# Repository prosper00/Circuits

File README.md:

Some KiCAD drawings I've make, of various useful circuits I've found online or reverse engineered (or adapted from someone else's design)

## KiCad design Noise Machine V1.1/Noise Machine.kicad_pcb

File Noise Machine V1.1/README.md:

# My attempt at an audio noise generator / sleep machine.
It's not 'white' or 'pink' or any particular color of noise - the filter stage shapes the output to whatever you feel sounds best. It's designed as a sleep aid to mask other noises.

### Goals:
- Run on 5V.
- Can provide 10 hours runtime on a small rechargeable USB power pack at moderate volume (so, let's say, we need this circuit to operate at < 100mA)
- Adjustable tone controls
- 'adequate' power output. A few mW to the speaker is quite sufficient to mask ambient sounds.
- uses 'jellybean' components that I have on hand

### Design:
- I settled on an avalanche noise source, running a small current above the breakdown voltage of an NPN be junction. Experimentally, I found that 8-9V is needed for a few of the common transistors I had on hand. I didn't see any significant difference between the few transistors that I tested, but that 12-15V produced much more amplitude.
- This is an audio device, so I don't need or want RF noise. Negative feedback on Q2 is applied with a 1nF capacitor (C3), to kill the RF as close to the source as possible.
- I'm running Q2 off of the 15V rail (more like +12V after diode drops etc.). However, Q2 output is only a few mV anyway and so it doesn't exceed the LM386 input. 
- I added a small adjustable filter section so that I could tune the output to a 'pleasing' sound. It's not super linear, and it does interact with the amplitude somewhat. 
- Because of the 5V supply voltage goal, I needed a low-current source of ~15V. Q3 and Q4 generate a square wave and power a small charge pump. A lot of the components in this voltage booster are less than optimal, though I did tweak them somewhat with the goal of producing sufficient current output, at reasonable efficiency. However, it works with the values I've chosen, more or less, though I did have some problems with the multivibrator failing to multivibrate. I added some startup diodes to increase its reliability, however, there's got to be a more elegant solution. 
- I used an LM386 to handle the output amplification, because I have a bunch. It provides more than sufficient output power. Really, it's overkill. 
- not shown in the circuit diagram is a 100uF and a 100nF decoupling capacitor near to where power comes into the PCB, right by the LM386 pins. This greatly helped with the multivibrator startup problems I had, and cleaned up its output signal. Using 31AWG magnet wire for the 'traces' on the protoboard is probably not the best idea, at least for the +5V/power GND connections.

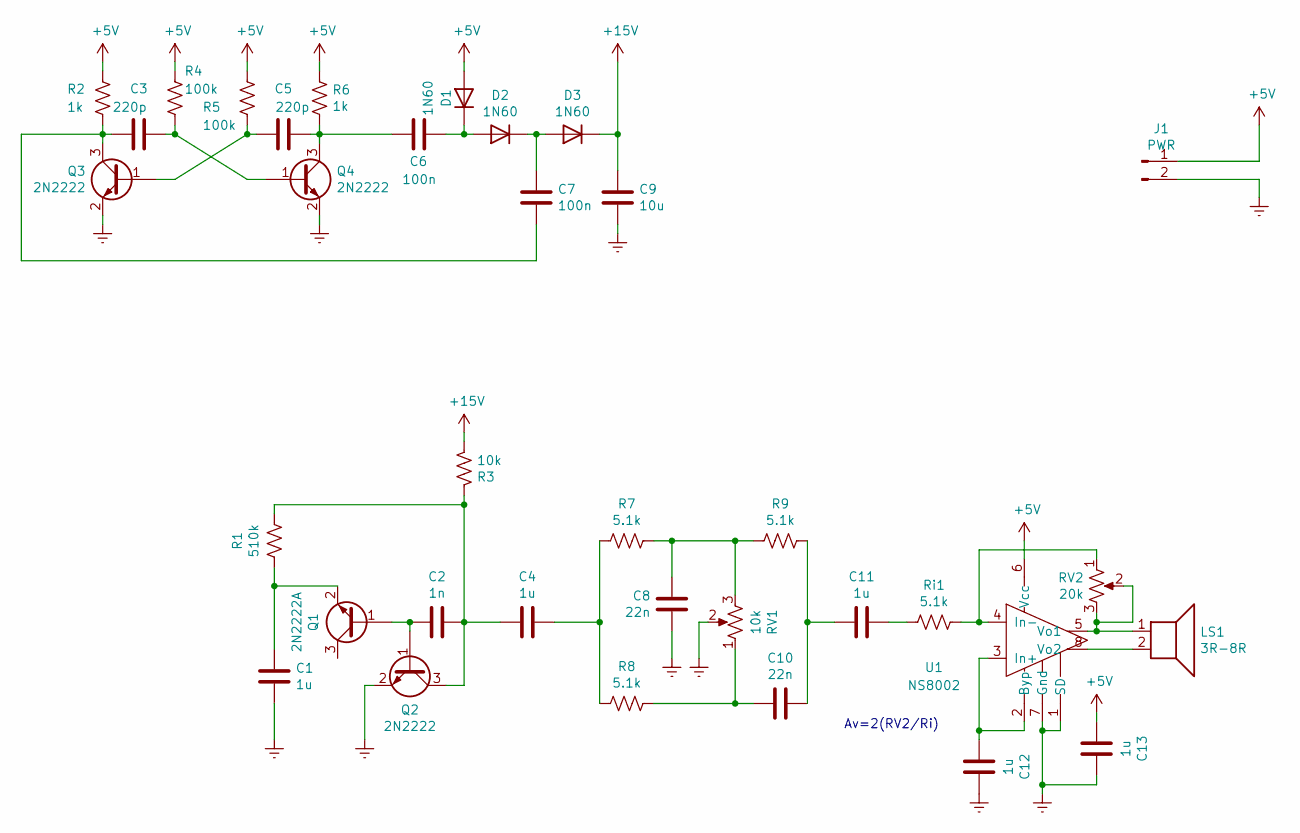
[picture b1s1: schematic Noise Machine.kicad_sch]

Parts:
C1, C4, C11, C12, C13: 1u; C_0603_1608Metric_Pad1.08x0.95mm_HandSolder
C2: 1n; C_0603_1608Metric_Pad1.08x0.95mm_HandSolder
C3, C5: 220p; C_0603_1608Metric_Pad1.08x0.95mm_HandSolder
C6, C7: 100n; C_0603_1608Metric_Pad1.08x0.95mm_HandSolder
C8, C10: 22n; C_0603_1608Metric_Pad1.08x0.95mm_HandSolder
C9: 10u; C_0603_1608Metric_Pad1.08x0.95mm_HandSolder
D1, D2, D3: 1N60; D_DO-35_SOD27_P5.08mm_Vertical_AnodeUp
J1: PWR; PinHeader_1x02_P2.54mm_Vertical
LS1: 3R-8R; PinHeader_1x02_P2.54mm_Vertical
Q1: 2N2222A; SOT-23
Q2, Q3, Q4: 2N2222; SOT-23
R1: 510k; R_0603_1608Metric_Pad0.98x0.95mm_HandSolder
R2, R6: 1k; R_0603_1608Metric_Pad0.98x0.95mm_HandSolder
R3: 10k; R_0603_1608Metric_Pad0.98x0.95mm_HandSolder
R4, R5: 100k; R_0603_1608Metric_Pad0.98x0.95mm_HandSolder
R7, R8, R9: 5.1k; R_0603_1608Metric_Pad0.98x0.95mm_HandSolder
RV1: 10k; PinHeader_1x03_P2.54mm_Vertical
RV2: 20k; PinHeader_1x02_P2.54mm_Vertical
Ri1: 5.1k; R_0603_1608Metric_Pad0.98x0.95mm_HandSolder
U1: NS8002; SO-8_3.9x4.9mm_P1.27mm

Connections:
+5V: C13.2, D1.2 (A), J1.1, R2.1, R4.1, R5.1, R6.1, U1.6 (Vcc)
+15V: C9.1, D3.1 (K), R3.2
Earth: C1.2, C8.1, C9.2, C12.1, C13.1, J1.2, Q2.2 (E), Q3.2 (E), Q4.2 (E), RV1.2, U1.1 (SD), U1.7 (Gnd)
unnamed: C1.1, Q1.2 (E), R1.2
unnamed: C2.1, C4.2, Q2.3 (C), R1.1, R3.1
unnamed: C2.2, Q1.1 (B), Q2.1 (B)
unnamed: C3.1, C7.2, Q3.3 (C), R2.2
unnamed: C3.2, Q4.1 (B), R4.2
unnamed: C4.1, R7.2, R8.2
unnamed: C5.1, C6.1, Q4.3 (C), R6.2
unnamed: C5.2, Q3.1 (B), R5.2
unnamed: C6.2, D1.1 (K), D2.2 (A)
unnamed: C7.1, D2.1 (K), D3.2 (A)
unnamed: C8.2, R7.1, R9.2, RV1.3
unnamed: C10.1, R8.1, RV1.1
unnamed: C10.2, C11.1, R9.1
unnamed: C11.2, Ri1.2
unnamed: C12.2, U1.2 (Byp), U1.3 (In+)
unnamed: LS1.1, RV2.2, RV2.3, U1.5 (Vo1)
unnamed: LS1.2, U1.8 (Vo2)
unnamed: RV2.1, Ri1.1, U1.4 (In-)

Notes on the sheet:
Av=2(RV2/Ri)

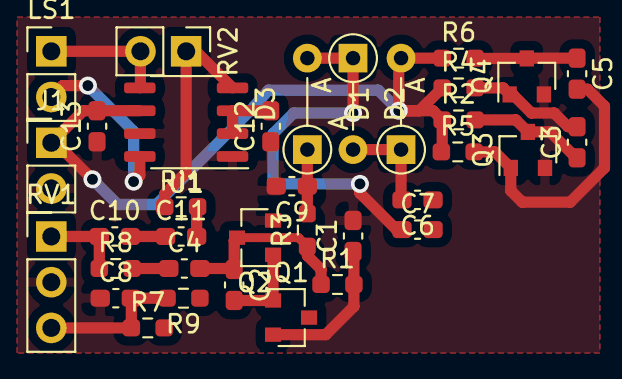
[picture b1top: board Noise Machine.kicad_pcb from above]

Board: 2 copper layers, 35 parts (0 on the bottom side), 21 nets.

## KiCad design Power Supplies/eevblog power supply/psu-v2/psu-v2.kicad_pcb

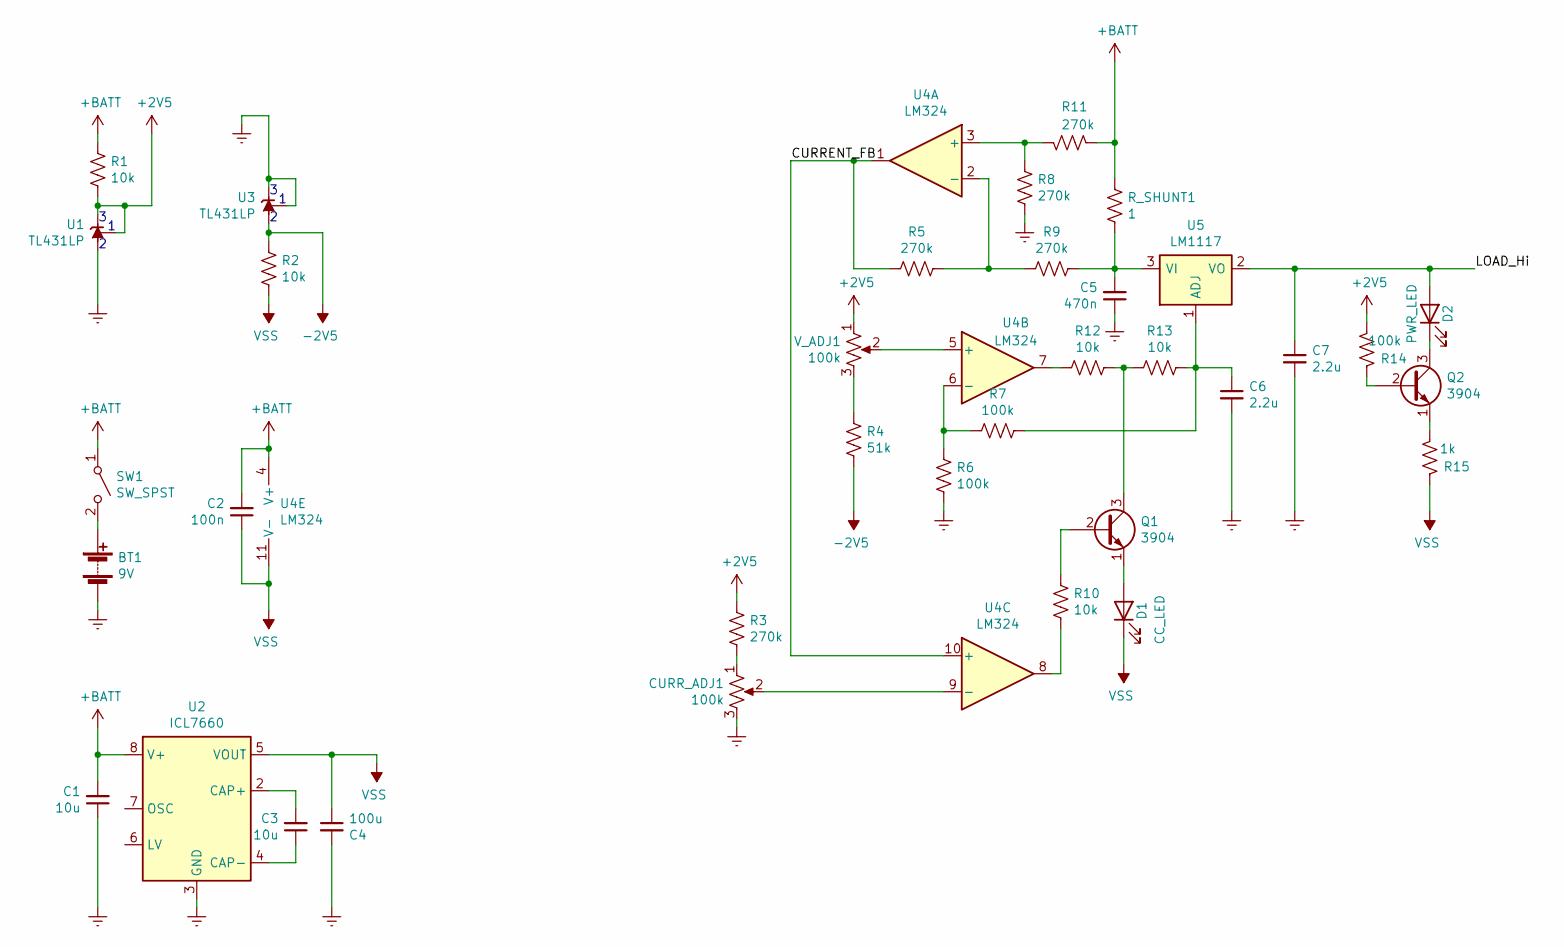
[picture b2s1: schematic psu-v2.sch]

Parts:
BT1: 9V; TerminalBlock_Altech_AK300-2_P5.00mm
C1, C3: 10u; C_Disc_D5.1mm_W3.2mm_P5.00mm
C2: 100n; C_Disc_D5.1mm_W3.2mm_P5.00mm
C4: 100u; C_Radial_D6.3mm_H7.0mm_P2.50mm
C5: 470n; C_Disc_D5.1mm_W3.2mm_P5.00mm
C6, C7: 2.2u; C_Disc_D5.1mm_W3.2mm_P5.00mm
CURR_ADJ1: 100k; Potentiometer_Alps_RK09K_Single_Horizontal
D1: CC_LED; LED_D3.0mm
D2: PWR_LED; LED_D3.0mm
Q1, Q2: 3904; TO-92L_Inline
R1, R2, R10, R12, R13: 10k; R_Axial_DIN0204_L3.6mm_D1.6mm_P5.08mm_Horizontal
R3, R5, R8, R9, R11: 270k; R_Axial_DIN0204_L3.6mm_D1.6mm_P5.08mm_Horizontal
R4: 51k; R_Axial_DIN0204_L3.6mm_D1.6mm_P5.08mm_Horizontal
R6, R7, R14: 100k; R_Axial_DIN0204_L3.6mm_D1.6mm_P5.08mm_Horizontal
R15: 1k; R_Axial_DIN0204_L3.6mm_D1.6mm_P5.08mm_Horizontal
R_SHUNT1: 1; R_Axial_DIN0414_L11.9mm_D4.5mm_P15.24mm_Horizontal
SW1: SW_SPST; PinHeader_1x02_P2.54mm_Vertical
U1, U3: TL431LP; TO-92_Inline
U2: ICL7660; DIP-8_W7.62mm_Socket
U4: LM324; DIP-14_W7.62mm_Socket
U5: LM1117; SOT-223-3_TabPin2
V_ADJ1: 100k; Potentiometer_Alps_RK09K_Single_Horizontal

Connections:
+2V5: R1.1, R3.2, R14.2, U1.1 (REF), U1.3 (K), V_ADJ1.1
+BATT: C1.2, C2.2, R1.2, R11.2, R_SHUNT1.2, SW1.1 (A), U2.8 (V+), U4.4 (V+)
-2V5: R2.2, R4.1, U3.2 (A)
/CURRENT_FB: R5.2, U4.1, U4.10 (+)
/LOAD_Hi: C7.1, D2.2 (A), U5.2 (VO)
Earth: BT1.2 (-), C1.1, C4.2, C5.1, C6.2, C7.2, CURR_ADJ1.3, R6.1, R8.1, U1.2 (A), U2.3 (GND), U3.1 (REF), U3.3 (K)
unnamed: BT1.1 (+), SW1.2 (B)
unnamed: C3.1, U2.4 (CAP-)
unnamed: C3.2, U2.2 (CAP+)
unnamed: C5.2, R9.1, R_SHUNT1.1, U5.3 (VI)
unnamed: C6.1, R7.2, R13.2, U5.1 (ADJ)
unnamed: CURR_ADJ1.1, R3.1
unnamed: CURR_ADJ1.2, U4.9 (-)
unnamed: D1.2 (A), Q1.1 (E)
unnamed: D2.1 (K), Q2.3 (C)
unnamed: Q1.2 (B), R10.1
unnamed: Q1.3 (C), R12.2, R13.1
unnamed: Q2.1 (E), R15.2
unnamed: Q2.2 (B), R14.1
unnamed: R4.2, V_ADJ1.3
unnamed: R5.1, R9.2, U4.2 (-)
unnamed: R6.2, R7.1, U4.6 (-)
unnamed: R10.2, U4.8
unnamed: R8.2, R11.1, U4.3 (+)
unnamed: R12.1, U4.7
unnamed: U4.5 (+), V_ADJ1.2
VSS: C2.1, C4.1, D1.1 (K), R2.1, R15.1, U2.5 (VOUT), U4.11 (V-)

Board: 2 copper layers, 36 parts (0 on the bottom side), 27 nets, no tracks yet.

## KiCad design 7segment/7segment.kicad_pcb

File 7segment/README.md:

see the project page on pcbway ( https://www.pcbway.com/project/shareproject/discrete_7_segment_LED.html ) if you want to order one. Or, use the provided gerber files with the manufacturer of your choosing

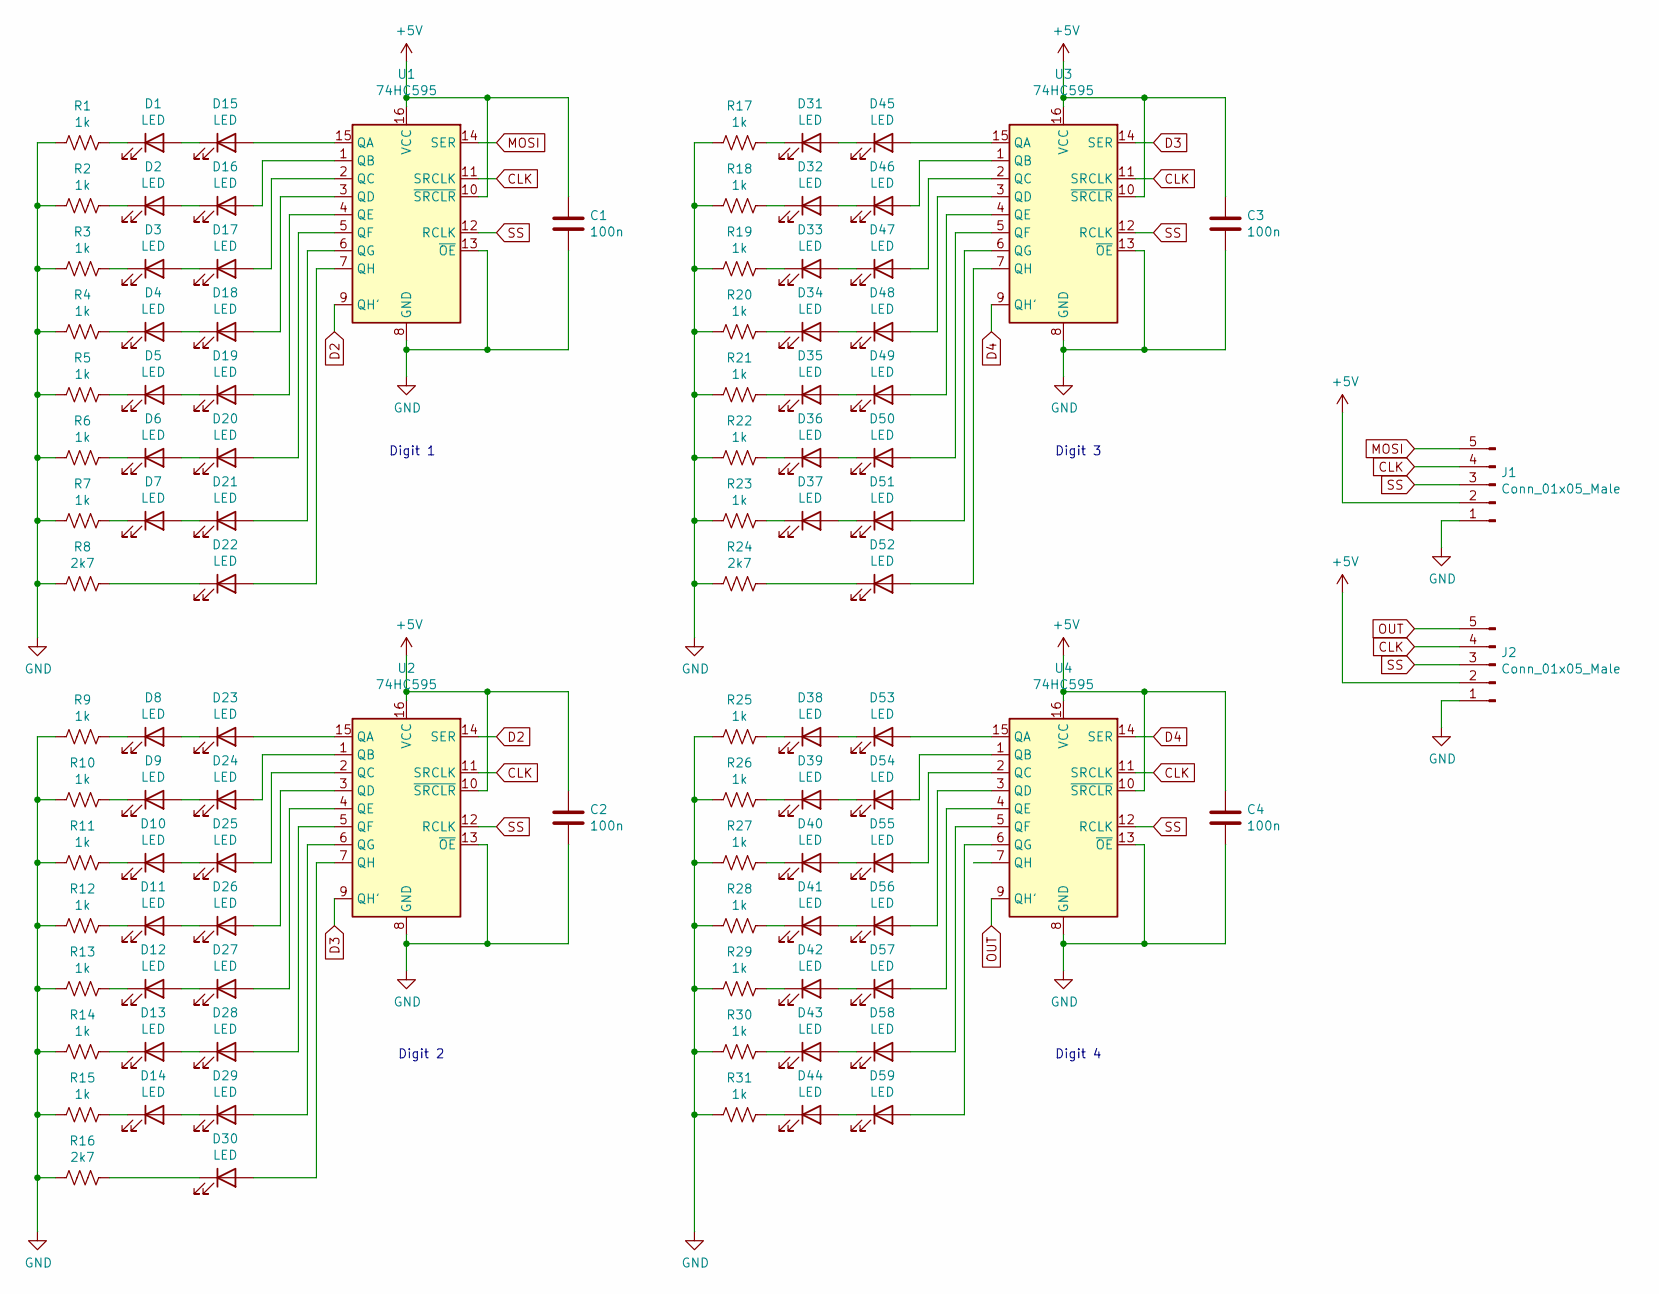
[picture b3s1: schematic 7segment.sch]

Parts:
C1, C2, C3, C4: 100n; C_Disc_D4.7mm_W2.5mm_P5.00mm
D1, D2, D3, D4, D5, D6, D7, D8, D9, D10, D11, D12, D13, D14, D15, D16, D17, D18, D19, D20, D21, D22, D23, D24, D25, D26, D27, D28, D29, D30, D31, D32, D33, D34, D35, D36, D37, D38, D39, D40, D41, D42, D43, D44, D45, D46, D47, D48, D49, D50, D51, D52, D53, D54, D55, D56, D57, D58, D59: LED; LED_D3.0mm
J1, J2: Conn_01x05_Male; PinHeader_1x05_P2.54mm_Vertical
R1, R2, R3, R4, R5, R6, R7, R9, R10, R11, R12, R13, R14, R15, R17, R18, R19, R20, R21, R22, R23, R25, R26, R27, R28, R29, R30, R31: 1k; R_Axial_DIN0204_L3.6mm_D1.6mm_P5.08mm_Horizontal
R8, R16, R24: 2k7; R_Axial_DIN0204_L3.6mm_D1.6mm_P5.08mm_Horizontal
U1, U2, U3, U4: 74HC595; DIP-16_W7.62mm

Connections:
+5V: C1.1, C2.1, C3.1, C4.1, J1.2, J2.2, U1.10 (~SRCLR), U1.16 (VCC), U2.10 (~SRCLR), U2.16 (VCC), U3.10 (~SRCLR), U3.16 (VCC), U4.10 (~SRCLR), U4.16 (VCC)
CLK: J1.4, J2.4, U1.11 (SRCLK), U2.11 (SRCLK), U3.11 (SRCLK), U4.11 (SRCLK)
D2: U1.9 (QH'), U2.14 (SER)
D3: U2.9 (QH'), U3.14 (SER)
D4: U3.9 (QH'), U4.14 (SER)
GND: C1.2, C2.2, C3.2, C4.2, J1.1, J2.1, R1.2, R2.2, R3.2, R4.2, R5.2, R6.2, R7.2, R8.2, R9.2, R10.2, R11.2, R12.2, R13.2, R14.2, R15.2, R16.2, R17.2, R18.2, R19.2, R20.2, R21.2, R22.2, R23.2, R24.2, R25.2, R26.2, R27.2, R28.2, R29.2, R30.2, R31.2, U1.8 (GND), U1.13 (~OE), U2.8 (GND), U2.13 (~OE), U3.8 (GND), U3.13 (~OE), U4.8 (GND), U4.13 (~OE)
MOSI: J1.5, U1.14 (SER)
unnamed: D1.1 (K), R1.1
unnamed: D1.2 (A), D15.1 (K)
unnamed: D2.1 (K), R2.1
unnamed: D3.1 (K), R3.1
unnamed: D4.1 (K), R4.1
unnamed: D5.1 (K), R5.1
unnamed: D6.1 (K), R6.1
unnamed: D7.1 (K), R7.1
unnamed: D8.1 (K), R9.1
unnamed: D9.1 (K), R10.1
unnamed: D10.1 (K), R11.1
unnamed: D10.2 (A), D25.1 (K)
unnamed: D11.1 (K), R12.1
unnamed: D11.2 (A), D26.1 (K)
unnamed: D12.1 (K), R13.1
unnamed: D12.2 (A), D27.1 (K)
unnamed: D13.1 (K), R14.1
unnamed: D13.2 (A), D28.1 (K)
unnamed: D14.1 (K), R15.1
unnamed: D14.2 (A), D29.1 (K)
unnamed: D15.2 (A), U1.15 (QA)
unnamed: D2.2 (A), D16.1 (K)
unnamed: D16.2 (A), U1.1 (QB)
unnamed: D3.2 (A), D17.1 (K)
unnamed: D17.2 (A), U1.2 (QC)
unnamed: D4.2 (A), D18.1 (K)
unnamed: D18.2 (A), U1.3 (QD)
unnamed: D5.2 (A), D19.1 (K)
unnamed: D19.2 (A), U1.4 (QE)
unnamed: D6.2 (A), D20.1 (K)
unnamed: D20.2 (A), U1.5 (QF)
unnamed: D7.2 (A), D21.1 (K)
unnamed: D21.2 (A), U1.6 (QG)
unnamed: D22.1 (K), R8.1
unnamed: D22.2 (A), U1.7 (QH)
unnamed: D8.2 (A), D23.1 (K)
unnamed: D23.2 (A), U2.15 (QA)
unnamed: D9.2 (A), D24.1 (K)
unnamed: D24.2 (A), U2.1 (QB)
unnamed: D25.2 (A), U2.2 (QC)
unnamed: D26.2 (A), U2.3 (QD)
unnamed: D27.2 (A), U2.4 (QE)
unnamed: D28.2 (A), U2.5 (QF)
unnamed: D29.2 (A), U2.6 (QG)
unnamed: D30.1 (K), R16.1
unnamed: D30.2 (A), U2.7 (QH)
unnamed: D31.1 (K), R17.1
unnamed: D31.2 (A), D45.1 (K)
unnamed: D32.1 (K), R18.1
unnamed: D32.2 (A), D46.1 (K)
unnamed: D33.1 (K), R19.1
unnamed: D33.2 (A), D47.1 (K)
unnamed: D34.1 (K), R20.1
unnamed: D34.2 (A), D48.1 (K)
unnamed: D35.1 (K), R21.1
unnamed: D35.2 (A), D49.1 (K)
unnamed: D36.1 (K), R22.1
unnamed: D36.2 (A), D50.1 (K)
unnamed: D37.1 (K), R23.1
unnamed: D37.2 (A), D51.1 (K)
unnamed: D38.1 (K), R25.1
unnamed: D38.2 (A), D53.1 (K)
unnamed: D39.1 (K), R26.1
unnamed: D39.2 (A), D54.1 (K)
unnamed: D40.1 (K), R27.1
unnamed: D40.2 (A), D55.1 (K)
unnamed: D41.1 (K), R28.1
unnamed: D41.2 (A), D56.1 (K)
unnamed: D42.1 (K), R29.1
unnamed: D42.2 (A), D57.1 (K)
unnamed: D43.1 (K), R30.1
unnamed: D43.2 (A), D58.1 (K)
unnamed: D44.1 (K), R31.1
unnamed: D44.2 (A), D59.1 (K)
unnamed: D45.2 (A), U3.15 (QA)
unnamed: D46.2 (A), U3.1 (QB)
unnamed: D47.2 (A), U3.2 (QC)
unnamed: D48.2 (A), U3.3 (QD)
unnamed: D49.2 (A), U3.4 (QE)
unnamed: D50.2 (A), U3.5 (QF)
unnamed: D51.2 (A), U3.6 (QG)
unnamed: D52.1 (K), R24.1
unnamed: D52.2 (A), U3.7 (QH)
unnamed: D53.2 (A), U4.15 (QA)
unnamed: D54.2 (A), U4.1 (QB)
unnamed: D55.2 (A), U4.2 (QC)
unnamed: D56.2 (A), U4.3 (QD)
unnamed: D57.2 (A), U4.4 (QE)
unnamed: D58.2 (A), U4.5 (QF)
unnamed: D59.2 (A), U4.6 (QG)
OUT: J2.5, U4.9 (QH')
SS: J1.3, J2.3, U1.12 (RCLK), U2.12 (RCLK), U3.12 (RCLK), U4.12 (RCLK)

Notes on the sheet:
Digit 1
Digit 2
Digit 3
Digit 4

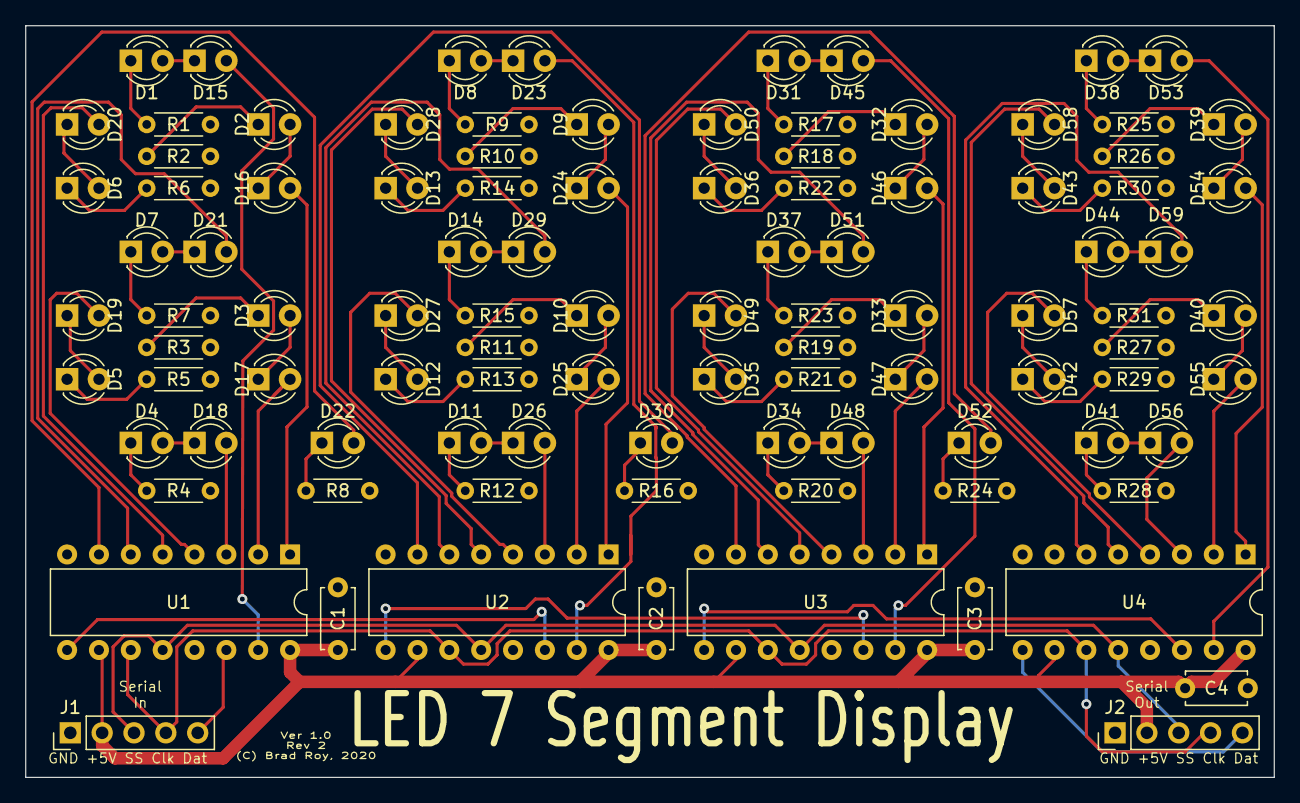
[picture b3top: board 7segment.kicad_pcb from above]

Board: 2 copper layers, 99.6 x 59.9 mm, 100 parts (0 on the bottom side), 99 nets.

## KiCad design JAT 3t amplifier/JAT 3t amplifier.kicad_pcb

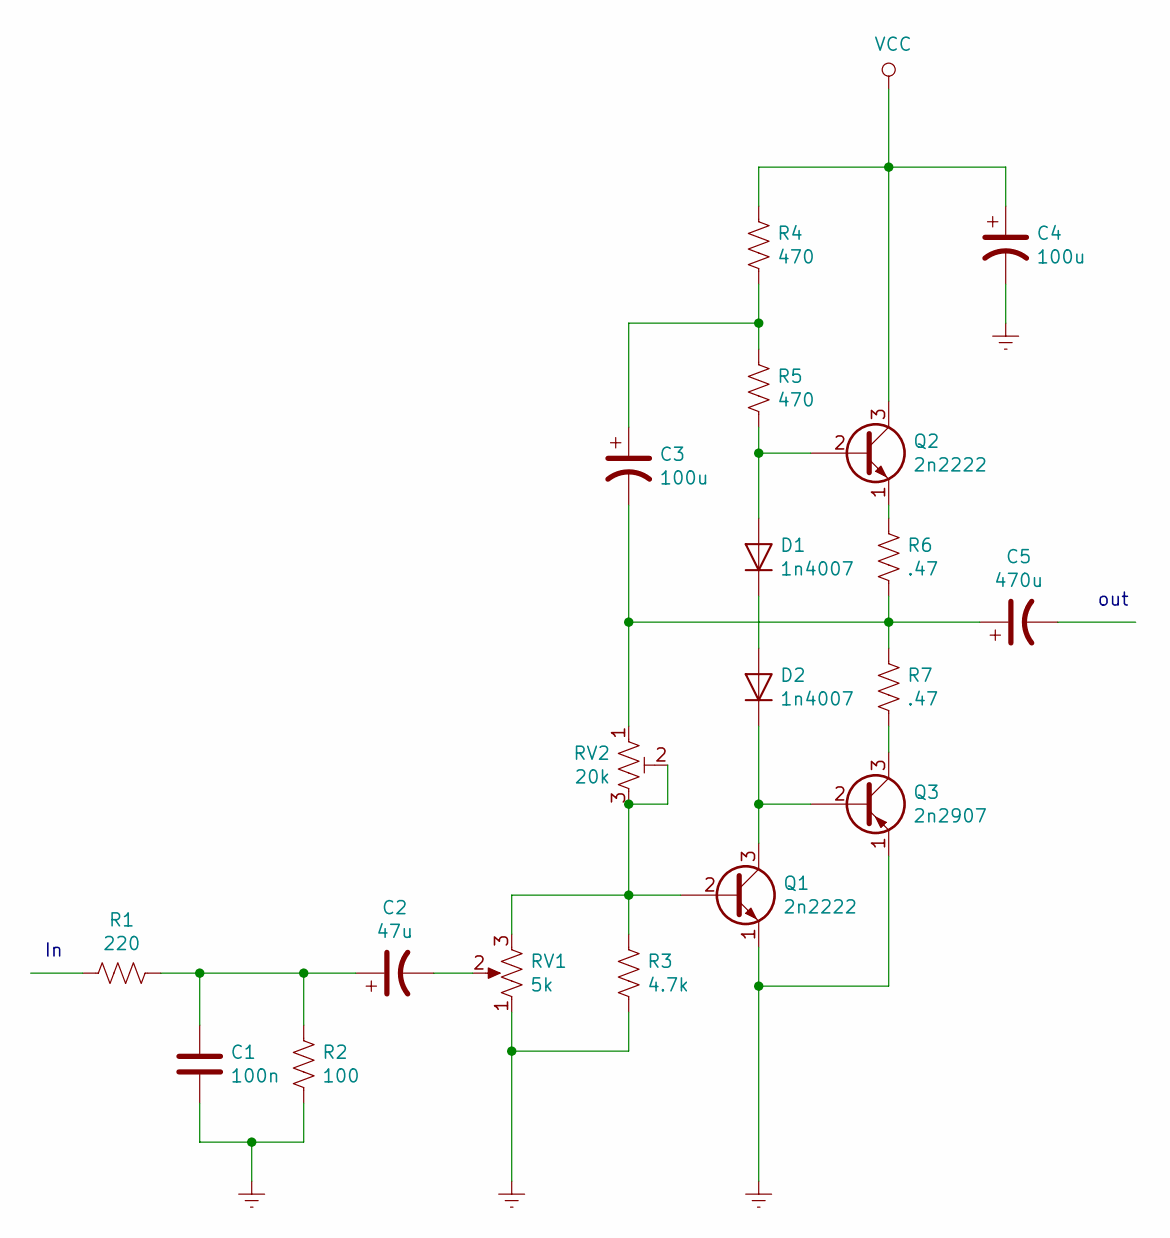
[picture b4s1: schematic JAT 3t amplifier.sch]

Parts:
C1: 100n; CP_Radial_Tantal_D6.0mm_P5.00mm
C2: 47u; CP_Radial_D6.3mm_P2.50mm
C3, C4: 100u; CP_Radial_D6.3mm_P2.50mm
C5: 470u; CP_Radial_D8.0mm_P2.50mm
D1, D2: 1n4007; D_DO-41_SOD81_P7.62mm_Horizontal
Q1, Q2: 2n2222; TO-92
Q3: 2n2907; TO-92
R1: 220; R_Axial_DIN0207_L6.3mm_D2.5mm_P7.62mm_Horizontal
R2: 100; R_Axial_DIN0207_L6.3mm_D2.5mm_P7.62mm_Horizontal
R3: 4.7k; R_Axial_DIN0207_L6.3mm_D2.5mm_P7.62mm_Horizontal
R4, R5: 470; R_Axial_DIN0207_L6.3mm_D2.5mm_P7.62mm_Horizontal
R6, R7: .47; R_Axial_DIN0207_L6.3mm_D2.5mm_P7.62mm_Horizontal
RV1: 5k; Potentiometer_ACP_CA9-H5_Horizontal
RV2: 20k; Potentiometer_ACP_CA9-H5_Horizontal

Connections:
Earth: C1.2, C4.2, Q1.1 (E), Q3.1 (E), R2.1, R3.2, RV1.1
unnamed: C1.1, C2.1, R1.1, R2.2
unnamed: C2.2, RV1.2
unnamed: C3.1, R4.2, R5.1
unnamed: C3.2, C5.1, R6.2, R7.1, RV2.1
unnamed: D1.1 (K), D2.2 (A)
unnamed: D1.2 (A), Q2.2 (B), R5.2
unnamed: D2.1 (K), Q1.3 (C), Q3.2 (B)
unnamed: Q1.2 (B), R3.1, RV1.3, RV2.2, RV2.3
unnamed: Q2.1 (E), R6.1
unnamed: Q3.3 (C), R7.2
VCC: C4.1, Q2.3 (C), R4.1

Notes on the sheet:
out

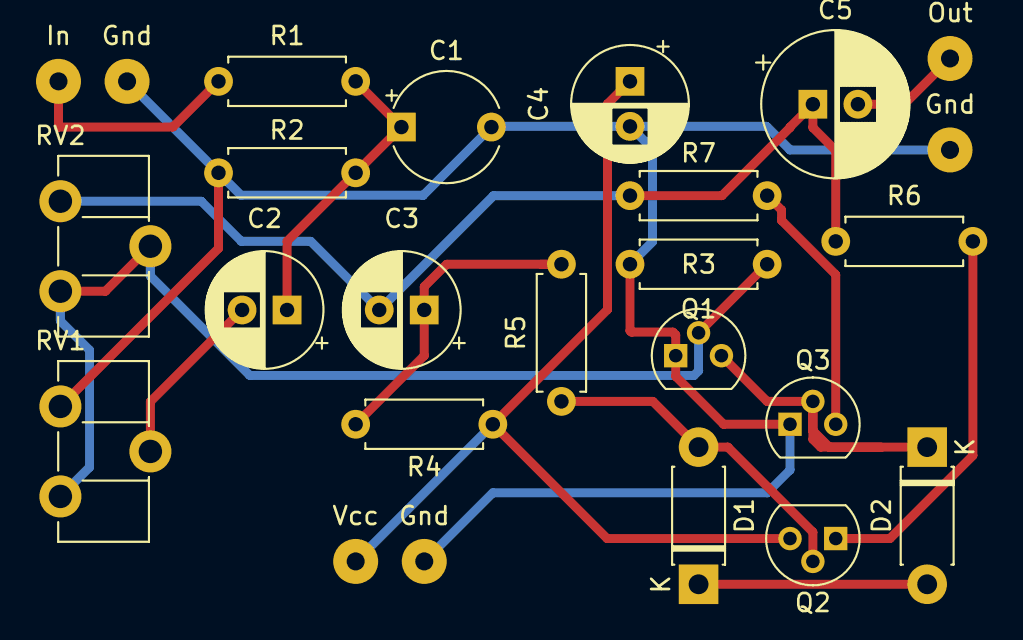
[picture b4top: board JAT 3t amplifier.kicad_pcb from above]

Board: 2 copper layers, 25 parts (0 on the bottom side), 12 nets.

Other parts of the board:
Gnd: SolderWirePad_1x01_Drill1mm
Gnd#2, Gnd#3: SolderWirePad_1x01_Drill1mm
In: SolderWirePad_1x01_Drill1mm
Out: SolderWirePad_1x01_Drill1mm
Vcc: SolderWirePad_1x01_Drill1mm

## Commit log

2020-09-04 Dave's SoftLatch Circuit (improved)
2020-12-16 added 7segment project
2020-12-16 organizing
2020-12-16 schematic added
2020-12-16 tweaks
2020-12-16 added label
2020-12-16 added pcbway-friendly gerbers
2020-12-17 PCBway-compatibility
2020-12-17 resized to <100mm
2020-12-17 Added daisy-chain connector
2020-12-17 updated images/gerbers
2021-01-04 Added Noise Machine V2
2021-01-04 fix Noise Machine V2
2021-06-24 Re-organize structure
2022-01-27 Updating latest
2022-01-27 updated pdf
2022-01-28 updates to voltage fedback
2022-02-01 update voltage feedback
2022-04-27 add new circuits
